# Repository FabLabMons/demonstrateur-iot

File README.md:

# Click IoT Board
## Purpose
This board aims to provide a starting point for building LTE Cat 1 projects for collecting data from a range of sensors.
These sensors can be connected on the I2C and SPI interfaces via a 4-wires connector.
Sensor boards will be hosted on a separate repository.

## Miscellaneous
We use the open source CAD tool KiCAD to build our boards: https://www.kicad.org/

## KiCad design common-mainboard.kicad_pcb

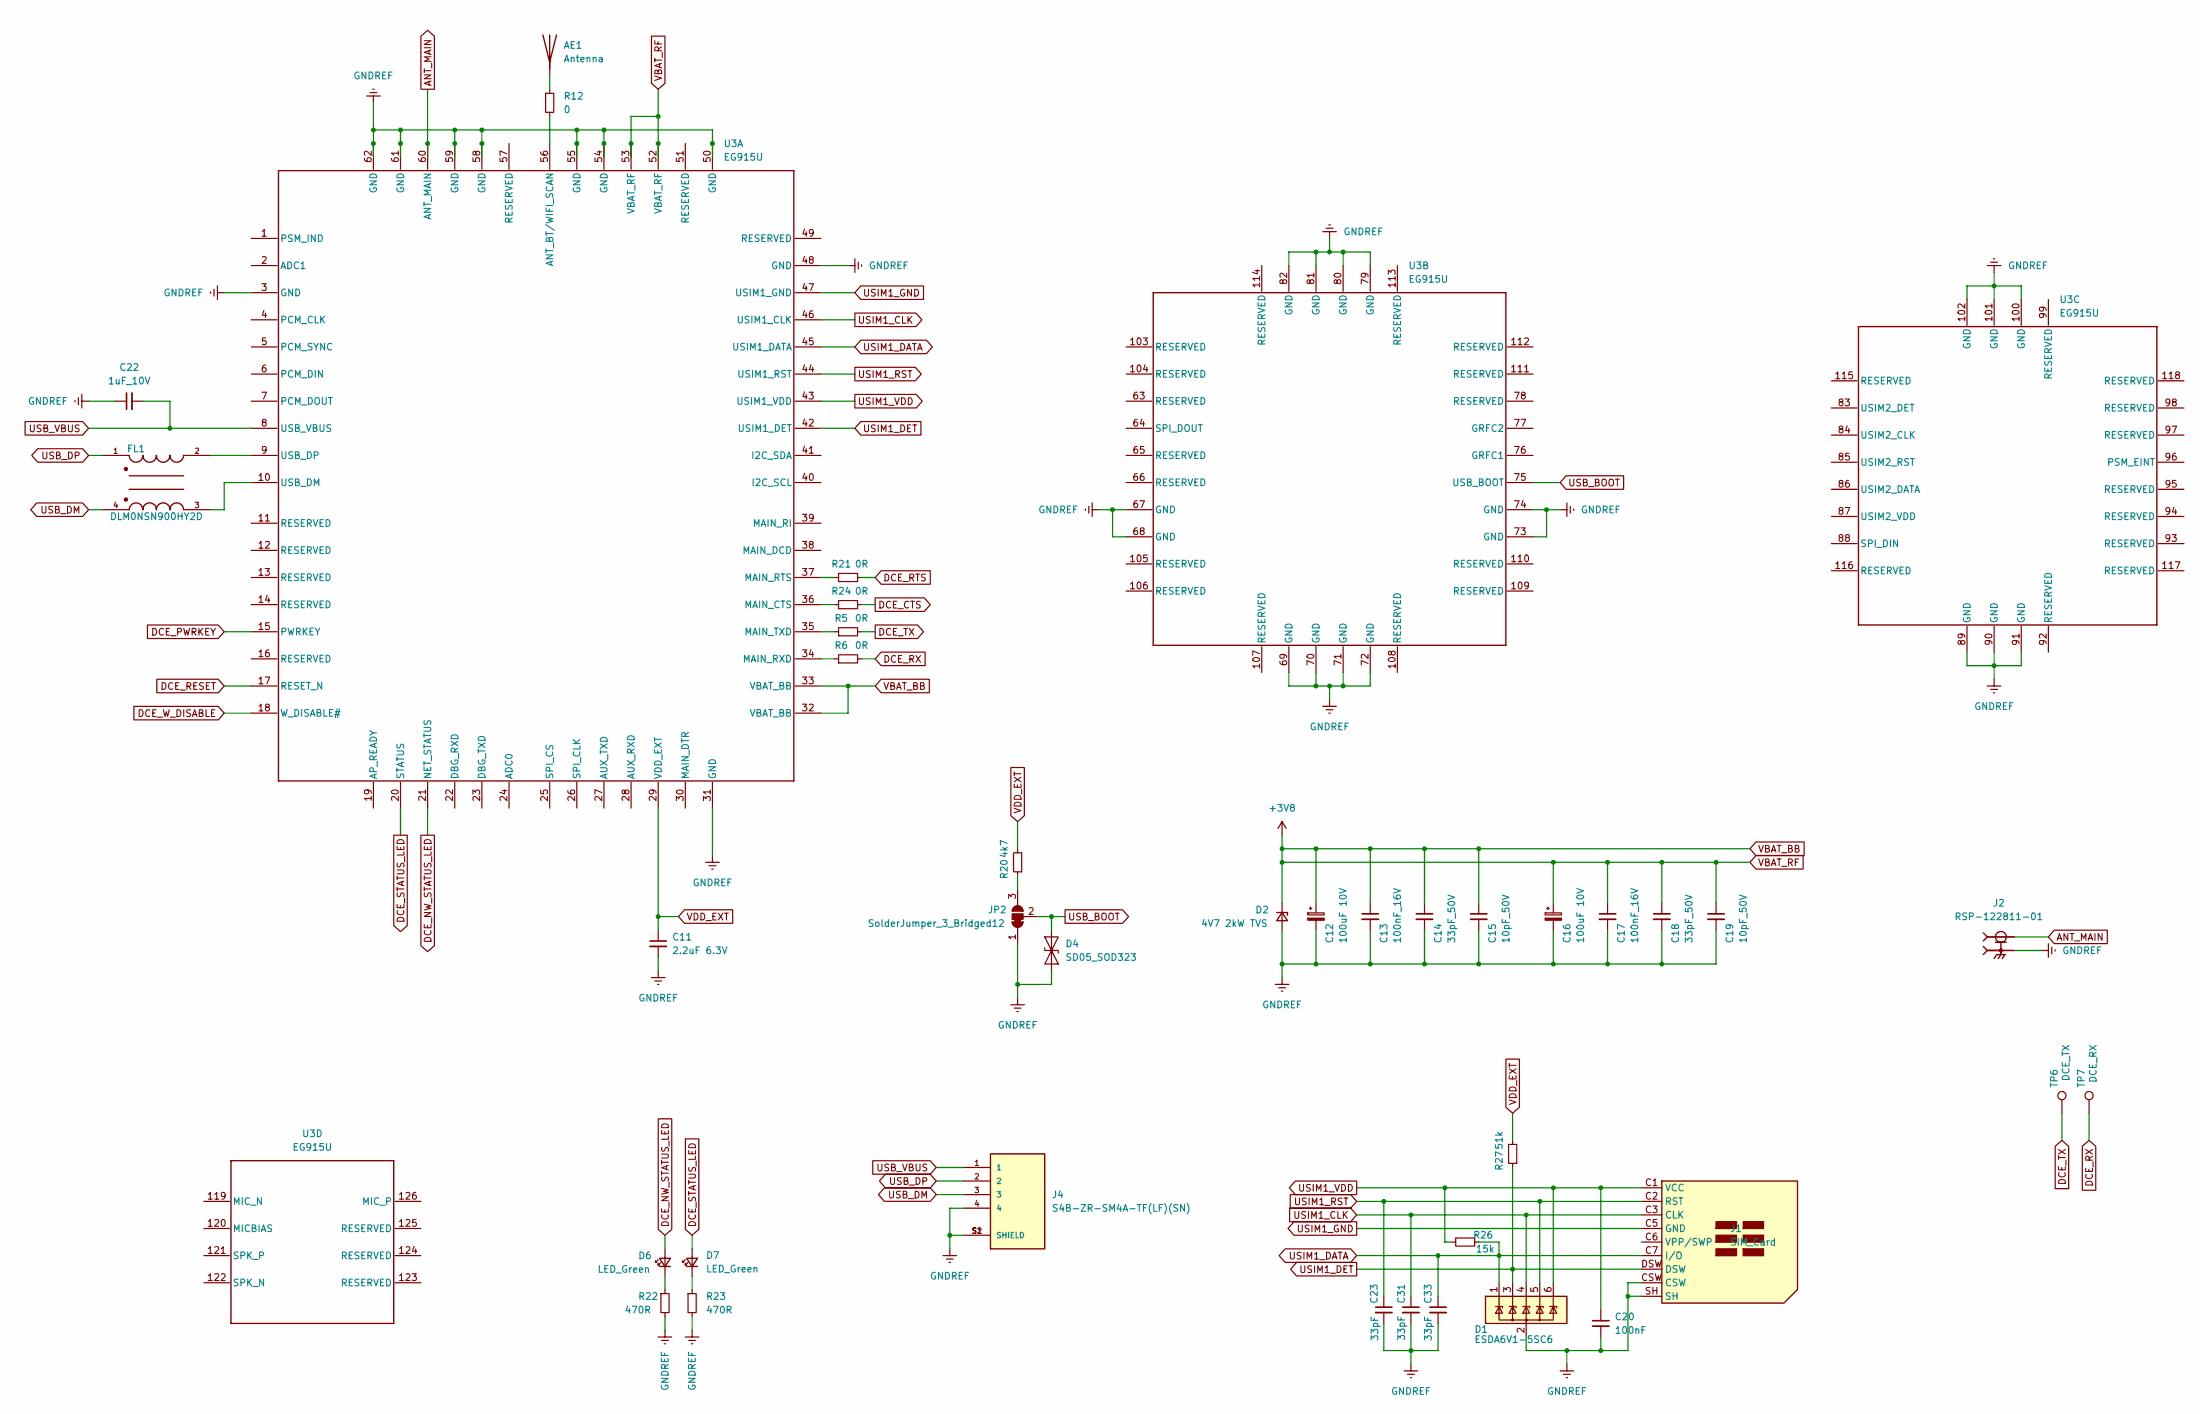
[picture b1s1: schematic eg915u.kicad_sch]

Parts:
AE1: Antenna; Quectel_YC0010AA
C11: 2.2uF 6.3V; C_0603_1608Metric
C12, C16: 100uF 10V; CP_EIA-6032-15_Kemet-U
C13, C17: 100nF_16V; C_0402_1005Metric
C14, C18: 33pF_50V; C_0402_1005Metric
C15, C19: 10pF_50V; C_0402_1005Metric
C20: 100nF; C_0402_1005Metric
C22: 1uF_10V; C_0603_1608Metric
C23, C31, C33: 33pF; C_0402_1005Metric
D1: ESDA6V1-5SC6; SOT-23-6
D2: 4V7 2kW TVS; D_SOD-323_HandSoldering
D4: SD05_SOD323; D_SOD-323_HandSoldering
D6, D7: LED_Green; LED_0805_2012Metric
FL1: DLM0NSN900HY2D; FIL_DLM0NSN900HY2D; PARTREV N/A
J1: SIM_Card; JAE_SIM_Card_SF72S006
J2: RSP-122811-01; SAMTEC_RSP-122811-01; PARTREV H
J4: S4B-ZR-SM4A-TF(LF)(SN); JST_S4B-ZR-SM4A-TF(LF)(SN); PARTREV N/A
JP2: SolderJumper_3_Bridged12; SolderJumper-3_P1.3mm_Bridged12_RoundedPad1.0x1.5mm
R5, R6, R21, R24: 0R; R_0402_1005Metric
R12: 0; R_0402_1005Metric
R20: 4k7; R_0402_1005Metric
R22, R23: 470R; R_0402_1005Metric
R26: 15k; R_0402_1005Metric
R27: 51k; R_0402_1005Metric
TP6: DCE_TX; TestPoint_Pad_D1.5mm
TP7: DCE_RX; TestPoint_Pad_D1.5mm
U3: EG915U; XCVR_EG91EXGA-128-SGNS

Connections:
ANT_MAIN: J2.1, U3.60 (ANT_MAIN)
DCE_CTS: R24.2; also elsewhere on the board
DCE_NW_STATUS_LED: D6.2 (A), U3.21 (NET_STATUS)
DCE_PWRKEY: U3.15 (PWRKEY); also elsewhere on the board
DCE_RESET: U3.17 (RESET_N); also elsewhere on the board
DCE_RTS: R21.2; also elsewhere on the board
DCE_RX: R6.2, TP7.1; also elsewhere on the board
DCE_STATUS_LED: D7.2 (A), U3.20 (STATUS)
DCE_TX: R5.2, TP6.1; also elsewhere on the board
DCE_W_DISABLE: U3.18 (W_DISABLE#); also elsewhere on the board
GNDREF: C11.2, C12.2, C13.2, C14.2, C15.2, C16.2, C17.2, C18.2, C19.2, C20.2, C22.1, C23.2, C31.2, C33.2, D1.2 (GND), D2.2 (A), D4.2 (A2), J1.CSW, J1.SH, J2.G1, J2.G2, J4.4, J4.S1 (SHIELD), J4.S2 (SHIELD), JP2.1 (A), R22.2, R23.2, U3.3 (GND), U3.31 (GND), U3.48 (GND), U3.50 (GND), U3.54 (GND), U3.55 (GND), U3.58 (GND), U3.59 (GND), U3.61 (GND), U3.62 (GND), U3.67 (GND), U3.68 (GND), U3.69 (GND), U3.70 (GND), U3.71 (GND), U3.72 (GND), U3.73 (GND), U3.74 (GND), U3.79 (GND), U3.80 (GND), U3.81 (GND), U3.82 (GND), U3.89 (GND), U3.90 (GND), U3.91 (GND), U3.100 (GND), U3.101 (GND), U3.102 (GND); also elsewhere on the board
unnamed: AE1.1 (A), R12.1
unnamed: D6.1 (K), R22.1
unnamed: D7.1 (K), R23.1
unnamed: FL1.2, U3.9 (USB_DP)
unnamed: FL1.3, U3.10 (USB_DM)
unnamed: JP2.3 (B), R20.1
unnamed: R5.1, U3.35 (MAIN_TXD)
unnamed: R6.1, U3.34 (MAIN_RXD)
unnamed: R12.2, U3.56 (ANT_BT/WIFI_SCAN)
unnamed: R21.1, U3.37 (MAIN_RTS)
unnamed: R24.1, U3.36 (MAIN_CTS)
USB_BOOT: D4.1 (A1), JP2.2 (C), U3.75 (USB_BOOT)
USB_DM: FL1.4, J4.3
USB_DP: FL1.1, J4.2
USB_VBUS: C22.2, J4.1, U3.8 (USB_VBUS)
USIM1_CLK: C31.1, D1.4 (IO3), J1.C3 (CLK), U3.46 (USIM1_CLK)
USIM1_DATA: C33.1, D1.1 (IO1), J1.C7 (I/O), R26.1, U3.45 (USIM1_DATA)
USIM1_DET: D1.3 (IO2), J1.DSW, R27.1, U3.42 (USIM1_DET)
USIM1_GND: J1.C5 (GND), U3.47 (USIM1_GND)
USIM1_RST: C23.1, D1.5 (IO4), J1.C2 (RST), U3.44 (USIM1_RST)
USIM1_VDD: C20.1, D1.6 (IO5), J1.C1 (VCC), R26.2, U3.43 (USIM1_VDD)
VBAT_BB: C12.1, C13.1, C14.1, C15.1, C16.1, C17.1, C18.1, C19.1, D2.1 (K), U3.32 (VBAT_BB), U3.33 (VBAT_BB), U3.52 (VBAT_RF), U3.53 (VBAT_RF); also elsewhere on the board
VDD_EXT: C11.1, R20.2, R27.2, U3.29 (VDD_EXT); also elsewhere on the board

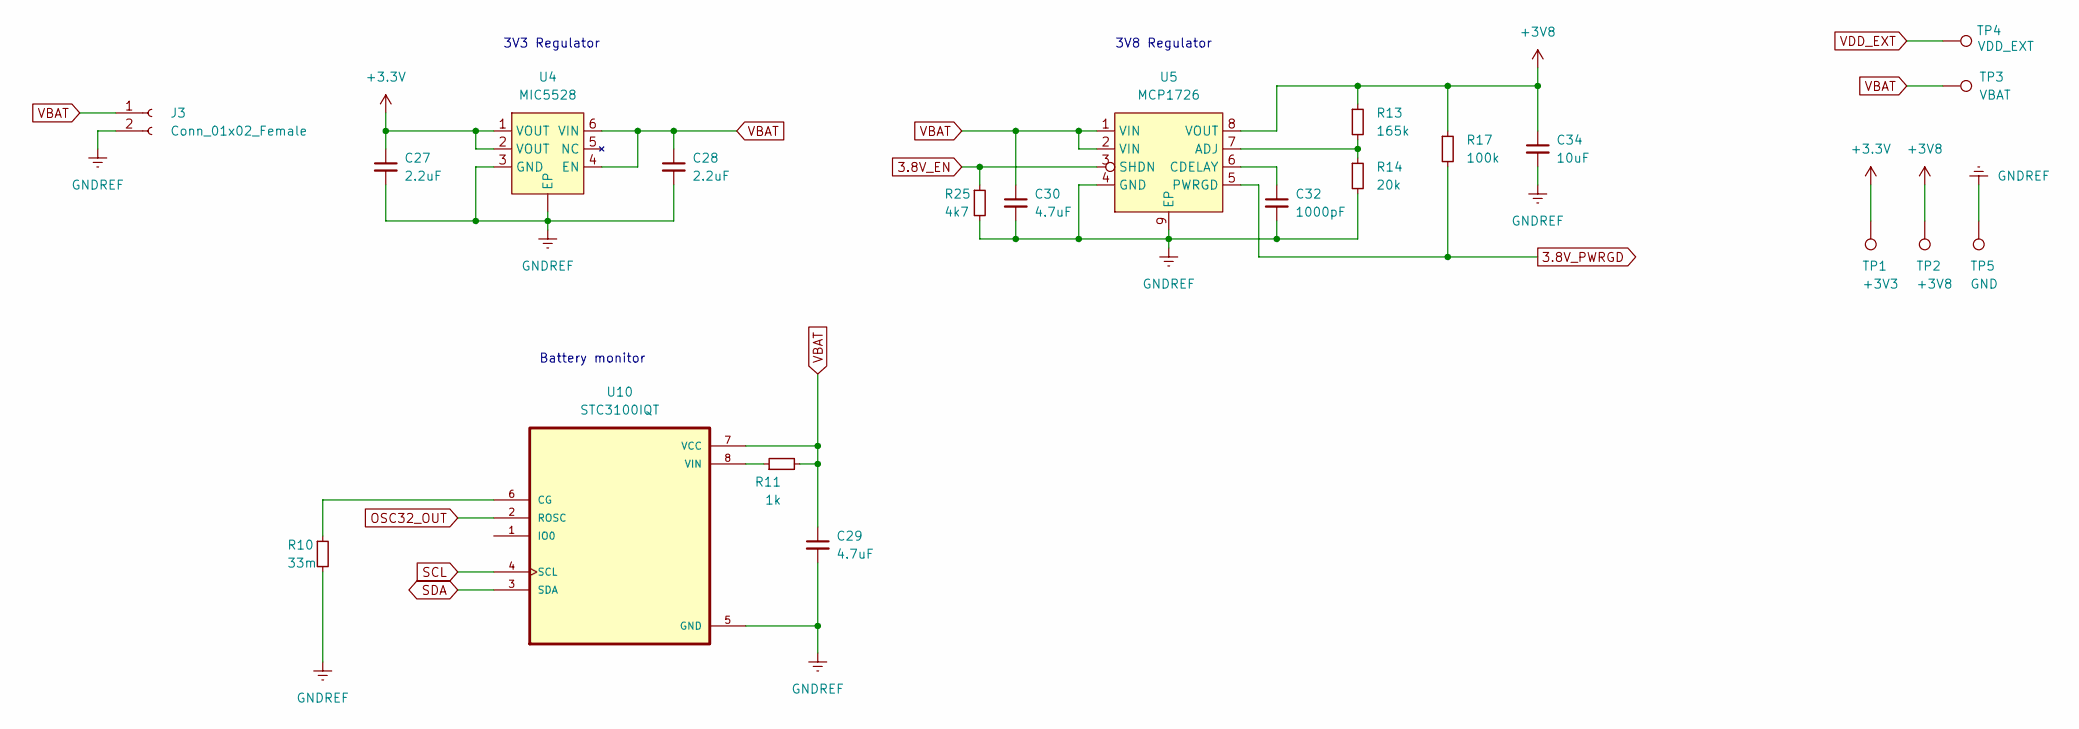
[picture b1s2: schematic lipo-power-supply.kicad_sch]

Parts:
C27, C28: 2.2uF; C_0603_1608Metric
C29, C30: 4.7uF; C_0603_1608Metric
C32: 1000pF; C_0402_1005Metric
C34: 10uF; C_0603_1608Metric
J3: Conn_01x02_Female; JST_PH_B2B-PH-SM4-TB_1x02-1MP_P2.00mm_Vertical
R10: 33m; R_0603_1608Metric
R11: 1k; R_0402_1005Metric
R13: 165k; R_0603_1608Metric
R14: 20k; R_0402_1005Metric
R17: 100k; R_0402_1005Metric
R25: 4k7; R_0402_1005Metric
TP1: +3V3; TestPoint_Pad_D1.5mm
TP2: +3V8; TestPoint_Pad_D1.5mm
TP3: VBAT; TestPoint_Pad_D1.5mm
TP4: VDD_EXT; TestPoint_Pad_D1.5mm
TP5: GND; TestPoint_Pad_D1.5mm
U4: MIC5528; DFN-6-1EP_1.2x1.2mm_P0.4mm_EP0.3x0.94mm_PullBack
U5: MCP1726; DFN-8-1EP_3x3mm_P0.65mm_EP1.55x2.4mm
U10: STC3100IQT; DFN-8-1EP_3x3mm_P0.5mm_EP1.65x2.38mm

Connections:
3.8V_EN: R25.1, U5.3 (SHDN); also elsewhere on the board
3.8V_PWRGD: R17.2, U5.5 (PWRGD); also elsewhere on the board
+3V3: C27.1, TP1.1, U4.1 (VOUT), U4.2 (VOUT); also elsewhere on the board
GNDREF: C27.2, C28.2, C29.2, C30.2, C32.2, C34.2, J3.2, R10.2, R14.2, R25.2, TP5.1, U4. (EP), U4.3 (GND), U5.4 (GND), U5.9 (EP), U10.5 (GND); also elsewhere on the board
unnamed: C32.1, U5.6 (CDELAY)
unnamed: R10.1, U10.6 (CG)
unnamed: R11.1, U10.8 (VIN)
unnamed: R13.2, R14.1, U5.7 (ADJ)
OSC32_OUT: U10.2 (ROSC); also elsewhere on the board
SCL: U10.4 (SCL); also elsewhere on the board
SDA: U10.3 (SDA); also elsewhere on the board
VBAT: C28.1, C29.1, C30.1, J3.1, R11.2, TP3.1, U4.4 (EN), U4.6 (VIN), U5.1 (VIN), U5.2 (VIN), U10.7 (VCC)
VBAT_BB: C34.1, R13.1, R17.1, TP2.1, U5.8 (VOUT); also elsewhere on the board
VDD_EXT: TP4.1; also elsewhere on the board

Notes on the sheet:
Battery monitor
3V8 Regulator
3V3 Regulator

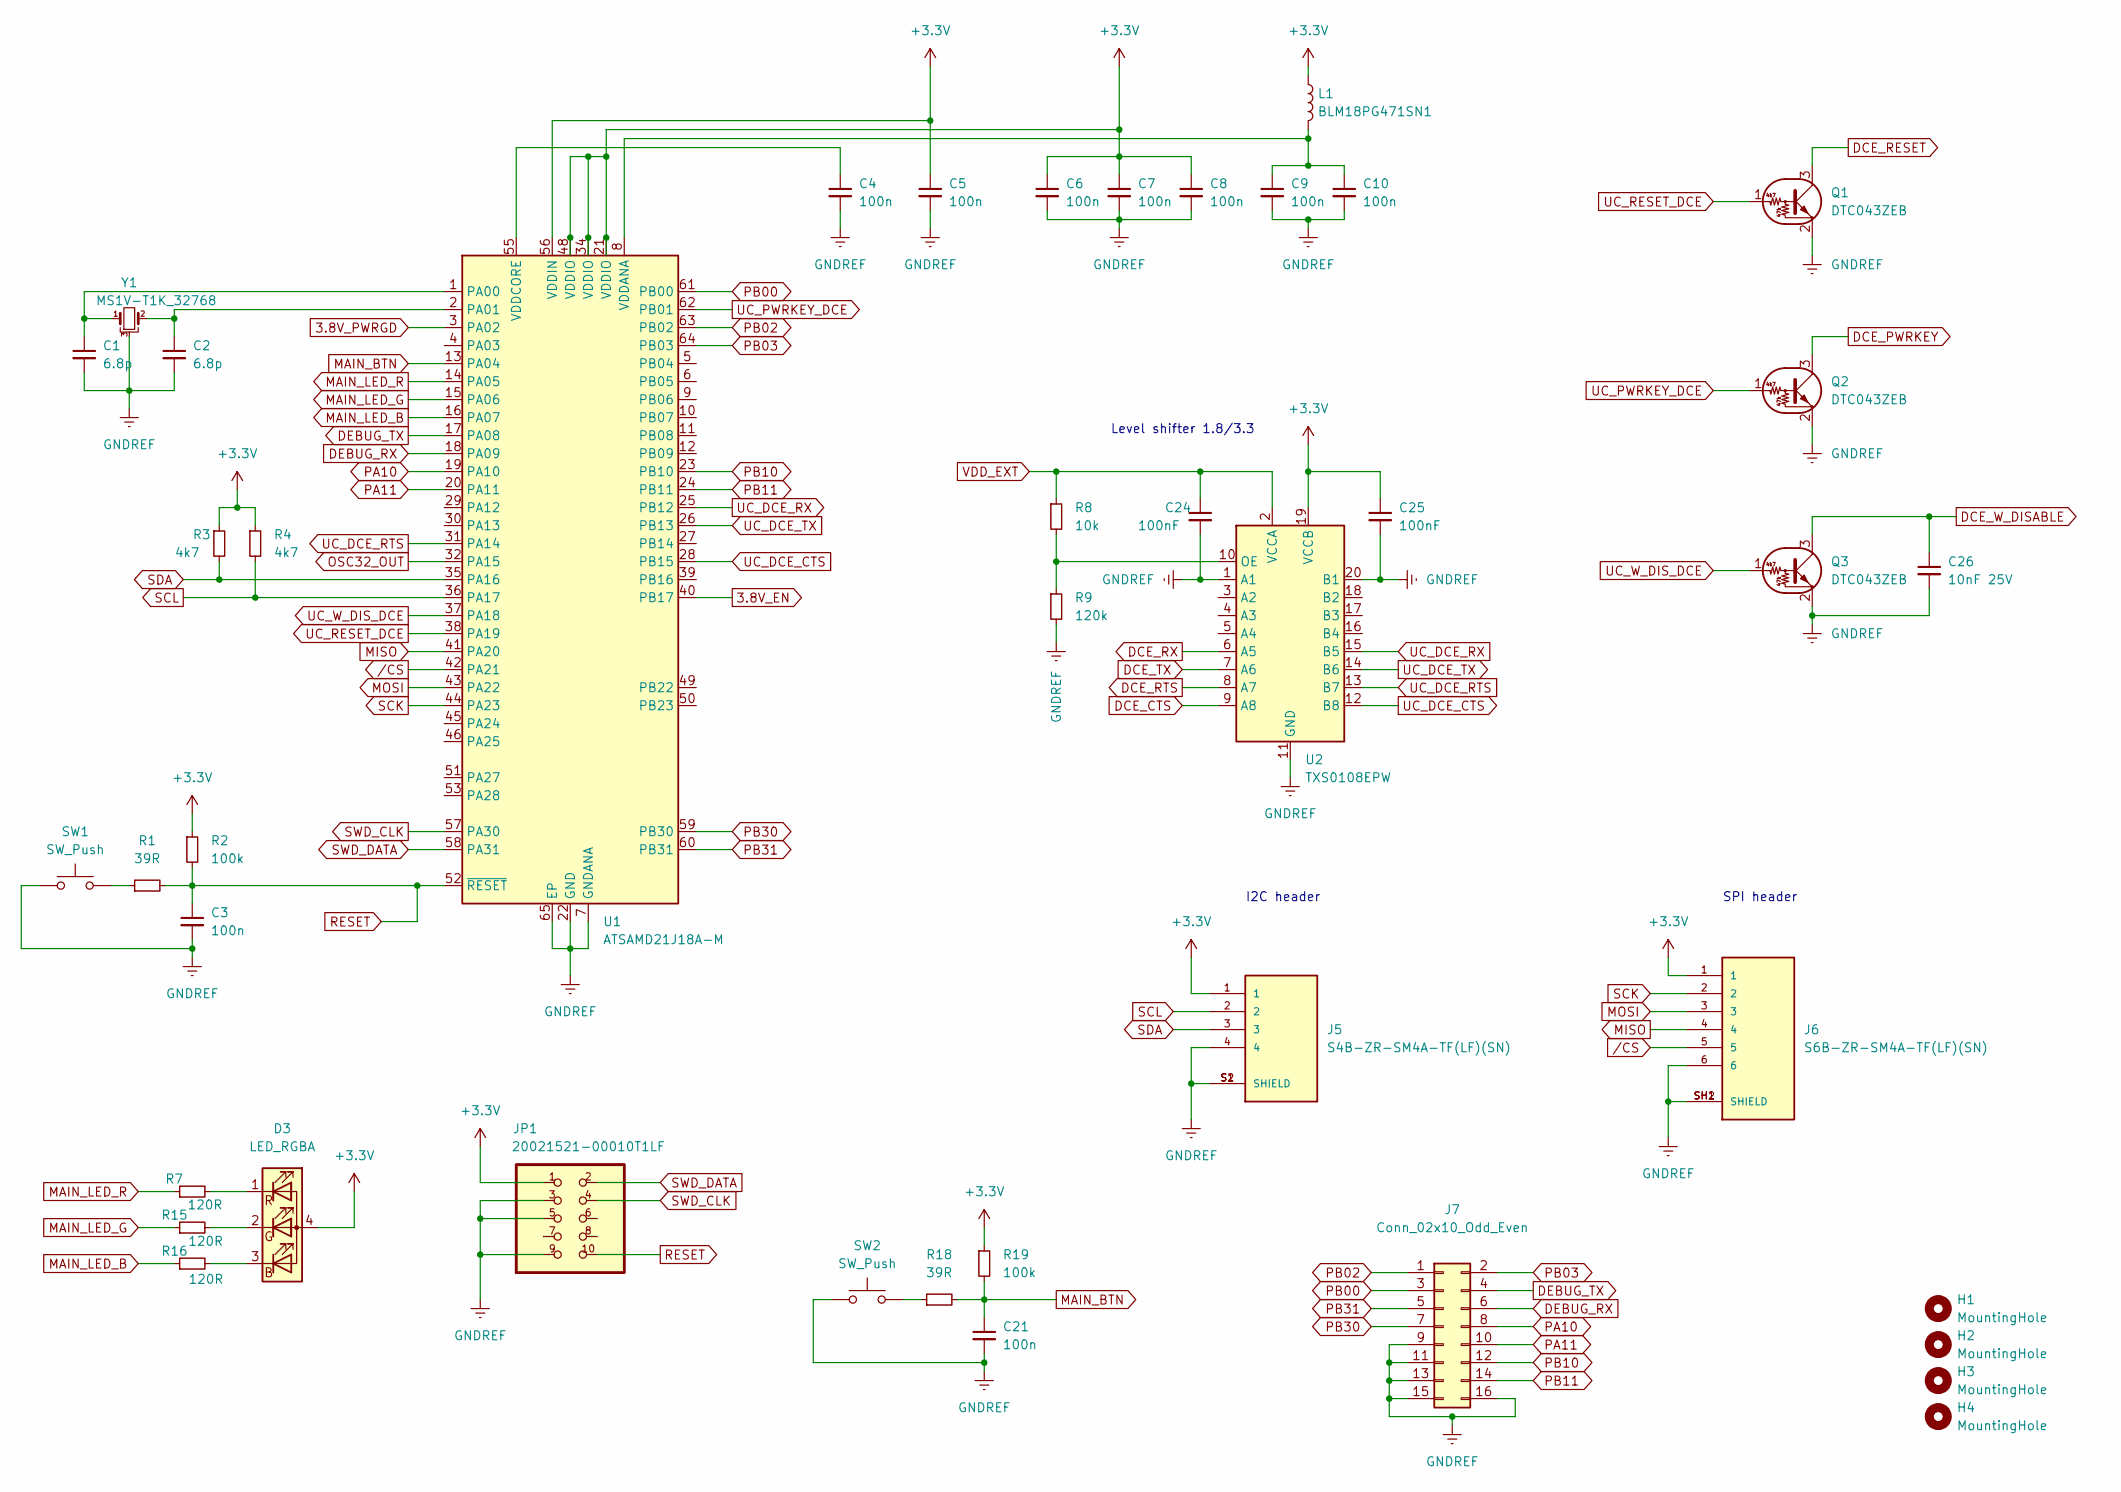
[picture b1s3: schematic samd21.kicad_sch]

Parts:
C1, C2: 6.8p; C_0402_1005Metric
C3, C4, C5, C6, C7, C8, C9, C10, C21: 100n; C_0402_1005Metric
C24, C25: 100nF; C_0402_1005Metric
C26: 10nF 25V; C_0402_1005Metric
D3: LED_RGBA; LED_RGB_Wuerth-PLCC4_3.2x2.8mm_150141M173100
H1, H2, H3, H4: MountingHole; MountingHole_3.2mm_M3
J5: S4B-ZR-SM4A-TF(LF)(SN); JST_S4B-ZR-SM4A-TF(LF)(SN); PARTREV N/A
J6: S6B-ZR-SM4A-TF(LF)(SN); JST_S6B-ZR-SM4A-TF(LF)(SN)
J7: Conn_02x10_Odd_Even; PinHeader_2x08_P2.54mm_Vertical
JP1: 20021521-00010T1LF
L1: BLM18PG471SN1; C_0603_1608Metric
Q1, Q2, Q3: DTC043ZEB; SOT-416
R1, R18: 39R; R_0402_1005Metric
R2, R19: 100k; R_0402_1005Metric
R3, R4: 4k7; R_0402_1005Metric
R7, R15, R16: 120R; R_0402_1005Metric
R8: 10k; R_0402_1005Metric
R9: 120k; R_0402_1005Metric
SW1, SW2: SW_Push; SW_Push_1P1T_NO_CK_KMR2
U1: ATSAMD21J18A-M; QFN-64-1EP_9x9mm_P0.5mm_EP4.7x4.7mm
U2: TXS0108EPW; TSSOP-20_4.4x6.5mm_P0.65mm
Y1: MS1V-T1K_32768; Crystal_SMD_MicroCrystal_MS1V-T1K

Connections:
3.8V_EN: U1.40 (PB17); also elsewhere on the board
3.8V_PWRGD: U1.3 (PA02); also elsewhere on the board
+3V3: C5.1, C6.1, C7.1, C8.1, C25.1, D3.4 (A), J5.1, J6.1, JP1.1, L1.1, R2.1, R3.1, R4.1, R19.1, U1.21 (VDDIO), U1.34 (VDDIO), U1.48 (VDDIO), U1.56 (VDDIN), U2.19 (VCCB); also elsewhere on the board
DCE_CTS: U2.9 (A8); also elsewhere on the board
DCE_PWRKEY: Q2.3 (C); also elsewhere on the board
DCE_RESET: Q1.3 (C); also elsewhere on the board
DCE_RTS: U2.8 (A7); also elsewhere on the board
DCE_RX: U2.6 (A5); also elsewhere on the board
DCE_TX: U2.7 (A6); also elsewhere on the board
DCE_W_DISABLE: C26.1, Q3.3 (C); also elsewhere on the board
DEBUG_RX: J7.6, U1.18 (PA09)
DEBUG_TX: J7.4, U1.17 (PA08)
GNDREF: C1.2, C2.2, C3.2, C4.2, C5.2, C6.2, C7.2, C8.2, C9.2, C10.2, C21.2, C24.2, C25.2, C26.2, J5.4, J5.S1 (SHIELD), J5.S2 (SHIELD), J6.6, J6.SH1 (SHIELD), J6.SH2 (SHIELD), J7.9, J7.11, J7.13, J7.15, J7.16, JP1.3, JP1.5, JP1.9, Q1.2 (E), Q2.2 (E), Q3.2 (E), R9.2, SW1.1, SW2.1, U1.7 (GNDANA), U1.22 (GND), U1.33 (GND), U1.47 (GND), U1.54 (GND), U1.65 (EP), U2.1 (A1), U2.11 (GND), U2.20 (B1), Y1.3; also elsewhere on the board
MAIN_BTN: C21.1, R18.2, R19.2, U1.13 (PA04)
MAIN_LED_B: R16.1, U1.16 (PA07)
MAIN_LED_G: R15.1, U1.15 (PA06)
MAIN_LED_R: R7.1, U1.14 (PA05)
MISO: J6.4, U1.41 (PA20)
MOSI: J6.3, U1.43 (PA22)
unnamed: C1.1, U1.1 (PA00), Y1.1
unnamed: C2.1, U1.2 (PA01), Y1.2
unnamed: C4.1, U1.55 (VDDCORE)
unnamed: C9.1, C10.1, L1.2, U1.8 (VDDANA)
unnamed: D3.1 (RK), R7.2
unnamed: D3.2 (GK), R15.2
unnamed: D3.3 (BK), R16.2
unnamed: R1.1, SW1.2
unnamed: R8.2, R9.1, U2.10 (OE)
unnamed: R18.1, SW2.2
OSC32_OUT: U1.32 (PA15); also elsewhere on the board
PA10: J7.8, U1.19 (PA10)
PA11: J7.10, U1.20 (PA11)
PB00: J7.3, U1.61 (PB00)
PB02: J7.1, U1.63 (PB02)
PB03: J7.2, U1.64 (PB03)
PB10: J7.12, U1.23 (PB10)
PB11: J7.14, U1.24 (PB11)
PB30: J7.7, U1.59 (PB30)
PB31: J7.5, U1.60 (PB31)
RESET: C3.1, JP1.10, R1.2, R2.2, U1.52 (~RESET)
SCK: J6.2, U1.44 (PA23)
SCL: J5.2, R4.2, U1.36 (PA17); also elsewhere on the board
SDA: J5.3, R3.2, U1.35 (PA16); also elsewhere on the board
SWD_CLK: JP1.4, U1.57 (PA30)
SWD_DATA: JP1.2, U1.58 (PA31)
UC_DCE_CTS: U1.28 (PB15), U2.12 (B8)
UC_DCE_RTS: U1.31 (PA14), U2.13 (B7)
UC_DCE_RX: U1.25 (PB12), U2.15 (B5)
UC_DCE_TX: U1.26 (PB13), U2.14 (B6)
UC_PWRKEY_DCE: Q2.1 (B), U1.62 (PB01)
UC_RESET_DCE: Q1.1 (B), U1.38 (PA19)
UC_W_DIS_DCE: Q3.1 (B), U1.37 (PA18)
VDD_EXT: C24.1, R8.1, U2.2 (VCCA); also elsewhere on the board
/CS: J6.5, U1.42 (PA21)

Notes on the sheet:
I2C header
Level shifter 1.8/3.3
SPI header

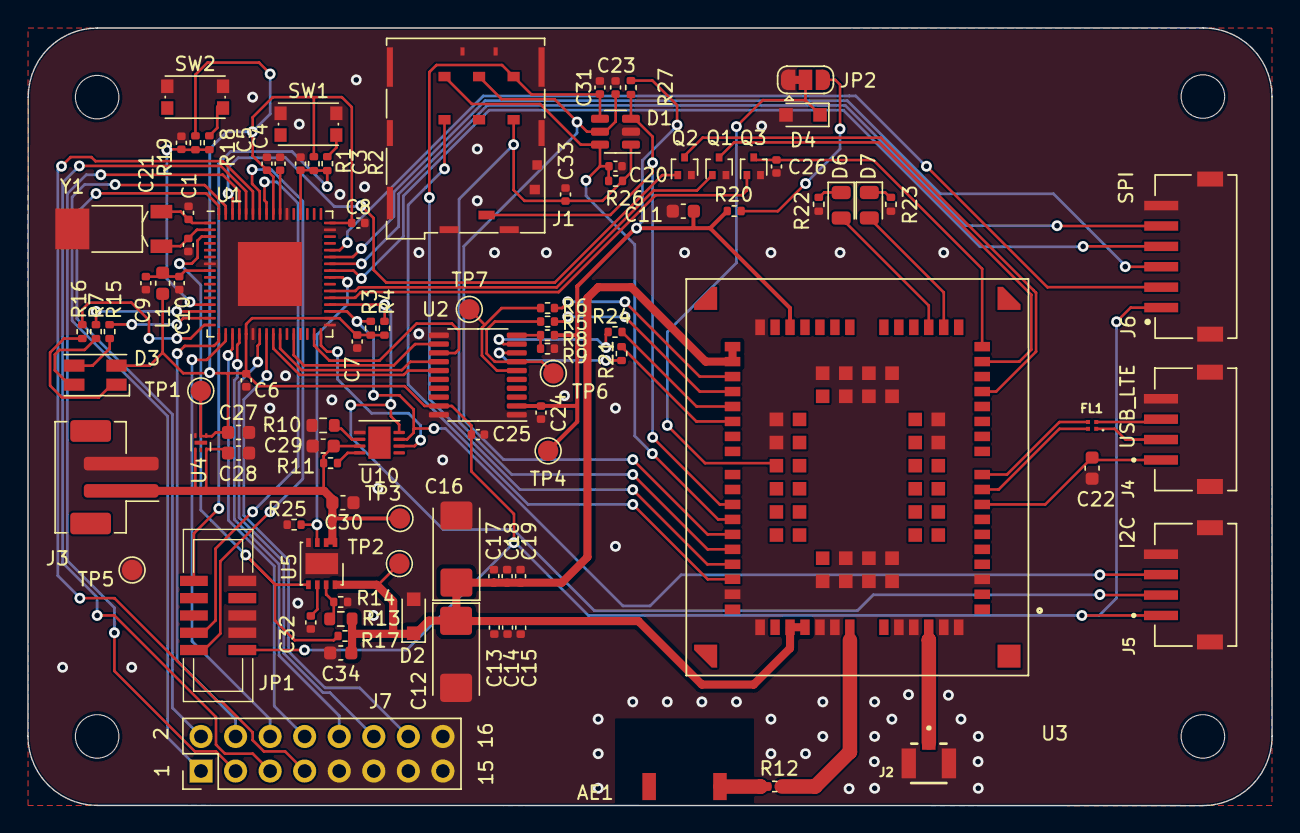
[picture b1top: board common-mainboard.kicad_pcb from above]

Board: 2 copper layers, 91.5 x 57.2 mm, 102 parts (0 on the bottom side), 84 nets.

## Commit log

2022-06-03 Create LICENSE
2022-06-08 Added files
2022-09-21 modified .gitignore
2022-09-21 eg915u: modified page layout, added USB upgrade support (sch + pcb)
2022-09-21 added UART flow control pins CTS and RTS
2022-09-21 added test point for VDD_EXT
2022-09-21 3.8V LDO: added output enable control from uc
2022-09-21 sim card: added RF filtering passive components
2022-09-28 added connectors for I2C and SPI extensions
2022-10-13 updated footprints and PCB
2022-10-14 fixed SIM card orientation
2022-10-14 [FAB] added board dimensions
2022-11-24 PCB: moved vias from underneath to outside of ICs
2022-11-24 ok before switching to EG91EX footprint
2023-01-25 Added IO and debug UART to pin header
2023-03-24 Added 4G modem UART test points
2023-06-16 Final prod version
